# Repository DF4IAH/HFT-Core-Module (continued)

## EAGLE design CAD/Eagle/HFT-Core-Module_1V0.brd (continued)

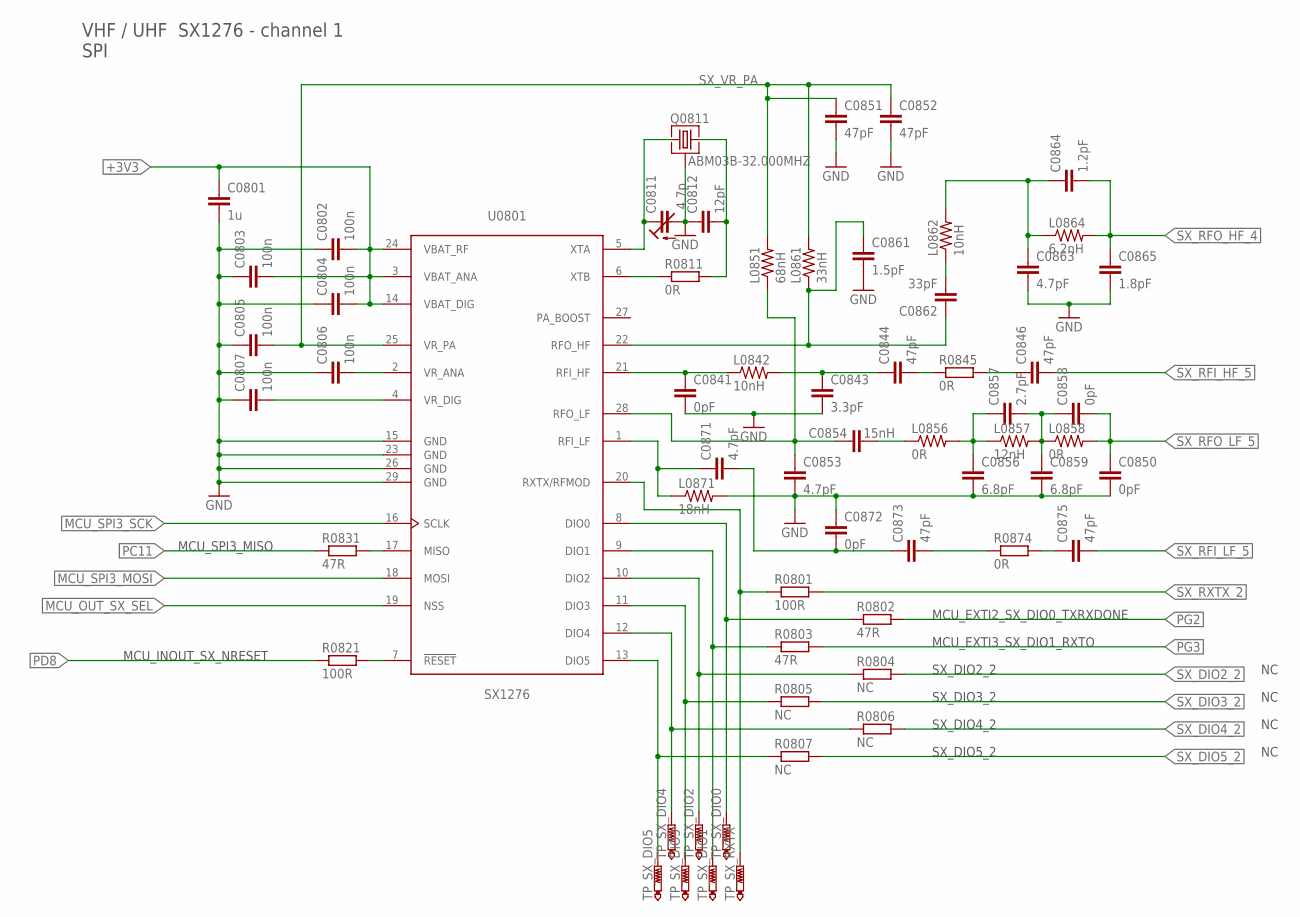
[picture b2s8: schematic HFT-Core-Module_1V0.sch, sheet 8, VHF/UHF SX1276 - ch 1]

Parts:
C0801: 1u; C0603
C0802, C0803, C0804, C0805, C0806, C0807: 100n; C0603
C0811: 4.7p; 3MM2_X_2MM5
C0812: 12pF; C0603
C0841, C0850, C0858, C0872: 0pF; C0603
C0843: 3.3pF; C0603
C0844, C0846, C0851, C0852, C0873, C0875: 47pF; C0603
C0853, C0863, C0871: 4.7pF; C0603
C0854: 15nH; C0603
C0856, C0859: 6.8pF; C0603
C0857: 2.7pF; C0603
C0861: 1.5pF; C0603
C0862: 33pF; C0603
C0864: 1.2pF; C0603
C0865: 1.8pF; C0603
L0842, L0862: 10nH; R0603
L0851: 68nH; R0603
L0856, L0858: 0R; R0603
L0857: 12nH; R0603
L0861: 33nH; R0603
L0864: 6.2nH; R0603
L0871: 18nH; R0603
Q0811: ABM03B-32.000MHZ; ABM03B
R0801, R0821: 100R; R0603
R0802, R0803, R0831: 47R; R0603
R0804, R0805, R0806, R0807: NC; R0603
R0811, R0845, R0874: 0R; R0603
TP_SX_DIO0, TP_SX_DIO1, TP_SX_DIO2, TP_SX_DIO3, TP_SX_DIO4, TP_SX_DIO5: PTR1TP06R; TP06R
TP_SX_RXTX: PTR1TP06R; TP06R
U0801: SX1276; QFN28-6X6-0P65-PAD

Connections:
+3V3: C0801.1, C0802.2, C0803.2, C0804.2, U0801.3 (VBAT_ANA), U0801.14 (VBAT_DIG), U0801.24 (VBAT_RF); also elsewhere on the board
GND: C0801.2, C0802.1, C0803.1, C0804.1, C0805.1, C0806.1, C0807.1, C0811.+ (A), C0812.1, C0841.2, C0843.2, C0850.2, C0851.2, C0852.2, C0853.2, C0856.2, C0859.2, C0861.2, C0863.2, C0865.2, C0872.1, L0871.2, Q0811.2 (3), Q0811.4 (3), U0801.15 (GND), U0801.23 (GND), U0801.26 (GND), U0801.29 (GND); also elsewhere on the board
MCU_OUT_SX_SEL: U0801.19 (NSS); also elsewhere on the board
MCU_SPI3_MOSI: U0801.18 (MOSI); also elsewhere on the board
MCU_SPI3_SCK: U0801.16 (SCLK); also elsewhere on the board
PC11: R0831.1; also elsewhere on the board
PD8: R0821.1; also elsewhere on the board
PG2: R0802.2; also elsewhere on the board
PG3: R0803.2; also elsewhere on the board
SX_DIO0: R0802.1, TP_SX_DIO0.TP, U0801.8 (DIO0)
SX_DIO1: R0803.1, TP_SX_DIO1.TP, U0801.9 (DIO1)
SX_DIO2: R0804.1, TP_SX_DIO2.TP, U0801.10 (DIO2)
SX_DIO2_2: R0804.2
SX_DIO3: R0805.1, TP_SX_DIO3.TP, U0801.11 (DIO3)
SX_DIO3_2: R0805.2
SX_DIO4: R0806.1, TP_SX_DIO4.TP, U0801.12 (DIO4)
SX_DIO4_2: R0806.2
SX_DIO5: R0807.1, TP_SX_DIO5.TP, U0801.13 (DIO5)
SX_DIO5_2: R0807.2
SX_MISO: R0831.2, U0801.17 (MISO)
SX_NRESET: R0821.2, U0801.7 (!RESET)
SX_RFI_HF: C0841.1, L0842.1, U0801.21 (RFI_HF)
SX_RFI_HF_2: C0843.1, C0844.1, L0842.2
SX_RFI_HF_3: C0844.2, R0845.1
SX_RFI_HF_4: C0846.1, R0845.2
SX_RFI_HF_5: C0846.2; also elsewhere on the board
SX_RFI_LF: C0871.1, L0871.1, U0801.1 (RFI_LF)
SX_RFI_LF_2: C0871.2, C0872.2, C0873.1
SX_RFI_LF_3: C0873.2, R0874.1
SX_RFI_LF_4: C0875.1, R0874.2
SX_RFI_LF_5: C0875.2; also elsewhere on the board
SX_RFO_HF: C0861.1, C0862.1, L0861.1, U0801.22 (RFO_HF)
SX_RFO_HF_2: C0862.2, L0862.1
SX_RFO_HF_3: C0863.1, C0864.1, L0862.2, L0864.1
SX_RFO_HF_4: C0864.2, C0865.1, L0864.2; also elsewhere on the board
SX_RFO_LF: C0853.1, C0854.1, L0851.1, U0801.28 (RFO_LF)
SX_RFO_LF_2: C0854.2, L0856.1
SX_RFO_LF_3: C0856.1, C0857.1, L0856.2, L0857.1
SX_RFO_LF_4: C0857.2, C0858.1, C0859.1, L0857.2, L0858.1
SX_RFO_LF_5: C0850.1, C0858.2, L0858.2; also elsewhere on the board
SX_RXTX: R0801.1, TP_SX_RXTX.TP, U0801.20 (RXTX/RFMOD)
SX_RXTX_2: R0801.2; also elsewhere on the board
SX_VR_ANA: C0806.2, U0801.2 (VR_ANA)
SX_VR_DIG: C0807.2, U0801.4 (VR_DIG)
SX_VR_PA: C0805.2, C0851.1, C0852.1, L0851.2, L0861.2, U0801.25 (VR_PA)
SX_XTA: C0811.- (E), Q0811.1, U0801.5 (XTA)
SX_XTB: R0811.1, U0801.6 (XTB)
SX_XTB_R: C0812.2, Q0811.3 (2), R0811.2

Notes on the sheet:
VHF / UHF SX1276 - channel 1 SPI
MCU_SPI3_MISO
MCU_INOUT_SX_NRESET
MCU_EXTI2_SX_DIO0_TXRXDONE
MCU_EXTI3_SX_DIO1_RXTO
SX_DIO2_2
SX_DIO3_2
SX_DIO4_2
SX_DIO5_2

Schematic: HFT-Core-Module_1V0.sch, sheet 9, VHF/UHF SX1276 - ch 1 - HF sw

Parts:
C0911, C0921, C0999: 1nF; C0603
C0991: 100pF HiQ; C0603
C0992, C0993: 330pF HiQ; C0603
C0994, C0996: 0nF HiQ; C0603
L0995: 0R; R0603
U0911, U0921, U0991: PE4259; SC-70_6-LEAD_2X1MM25_0P65

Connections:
+3V3: C0911.1, C0921.1, C0999.1, U0911.6 (VDD_!CTRL), U0921.6 (VDD_!CTRL), U0991.6 (VDD_!CTRL); also elsewhere on the board
CH1_ANT: C0996.1, L0995.2; also elsewhere on the board
GND: C0911.2, C0921.2, C0994.2, C0996.2, C0999.2, U0911.2 (GND), U0921.2 (GND), U0991.2 (GND); also elsewhere on the board
MCU_SX_TX_RX_CTRL: U0991.4 (CTRL); also elsewhere on the board
SX_ANT_1: C0993.1, U0991.5 (RFC)
SX_ANT_2: C0993.2, C0994.1, L0995.1
SX_HF_1: C0991.1, U0911.5 (RFC)
SX_HF_2: C0991.2, U0991.1 (RF1)
SX_LF_1: C0992.1, U0921.5 (RFC)
SX_LF_2: C0992.2, U0991.3 (RF2)
SX_RFI_HF_5: U0911.3 (RF2); also elsewhere on the board
SX_RFI_LF_5: U0921.3 (RF2); also elsewhere on the board
SX_RFO_HF_4: U0911.1 (RF1); also elsewhere on the board
SX_RFO_LF_5: U0921.1 (RF1); also elsewhere on the board
SX_RXTX_2: U0911.4 (CTRL), U0921.4 (CTRL); also elsewhere on the board

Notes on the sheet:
HF: high / LF: low

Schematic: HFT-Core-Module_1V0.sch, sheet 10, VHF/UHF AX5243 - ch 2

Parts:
C1001, C1002, C1003: 100nF; C0603
C_AX_A2, C_AX_A3: 4.7pF; C0603
C_AX_B2: 4.7pF; C0603
C_AX_C1, C_AX_C2: 0pF; C0603
C_AX_F2: 4.7pF; C0603
C_AX_M1: 4.7pF; C0603
C_AX_M2: 0pF; C0603
C_AX_T1, C_AX_T2: 4.3pF; C0603
L_AX_1: 22nH; R0603
L_AX_B1, L_AX_B2: 22nH; R0603
L_AX_C1, L_AX_C2: 100nH; R0603
L_AX_F1: 22nH; R0603
L_AX_T1, L_AX_T2: 43nH; R0603
Q0911: ABM3B-16MHZ-10-R50-1-U; ABM03B
R1021, R1041, R1051, R1061: 47R; R0603
R1031, R1032: 100kR; R0603
TP_AX_ADC1, TP_AX_ADC2: PTR1TP06R; TP06R
TP_AX_IRQ: PTR1TP06R; TP06R
TP_AX_TCXO_EN: PTR1TP06R; TP06R
U0901: AX5243; QFN20-4X4-0P5-PAD

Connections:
+3V3: C1001.1, U0901.16 (VDD_IO); also elsewhere on the board
AX_8MHZ: R1021.2; also elsewhere on the board
AX_ADC1: R1031.1, TP_AX_ADC1.TP, U0901.17 (GPADC1)
AX_ADC2: R1032.1, TP_AX_ADC2.TP, U0901.18 (GPADC2)
AX_ANTN: C_AX_C2.1, C_AX_T2.1, L_AX_C2.1, U0901.4 (ANTN)
AX_ANTP: C_AX_C1.1, C_AX_T1.1, L_AX_C1.1, U0901.3 (ANTP)
AX_B1: C_AX_M1.1, L_AX_B1.1, L_AX_T1.2
AX_B2: C_AX_B2.1, C_AX_M2.1, L_AX_B2.2, L_AX_T2.2
AX_CLK16N: Q0911.1, U0901.19 (CLK16N)
AX_CLK16P: Q0911.3 (2), U0901.20 (CLK16P)
AX_COMB: C_AX_A2.1, C_AX_B2.2, C_AX_F2.1, L_AX_B1.2, L_AX_F1.1
AX_GPIO1: R1061.2, TP_AX_TCXO_EN.TP, U0901.15 (TCXO_EN)
AX_IRQ: R1051.2, TP_AX_IRQ.TP, U0901.14 (IRQ)
AX_L1: L_AX_1.1, U0901.8 (L1)
AX_L2: L_AX_1.2, U0901.7 (L2)
AX_SYSCLK: R1021.1, U0901.9 (SYSCLK)
AX_T1: C_AX_T1.2, L_AX_T1.1
AX_T2: C_AX_T2.2, L_AX_T2.1
AX_VDD1: C1002.2, U0901.1 (VDD_ANA)
AX_VDD5: C1003.2, U0901.5 (VDD_ANA)
CH2_ANT: C_AX_A3.1, C_AX_F2.2, L_AX_F1.2; also elsewhere on the board
GND: C1001.2, C1002.1, C1003.1, C_AX_A2.2, C_AX_A3.2, C_AX_C1.2, C_AX_C2.2, C_AX_M1.2, C_AX_M2.2, L_AX_B2.1, L_AX_C1.2, L_AX_C2.2, Q0911.2 (3), Q0911.4 (3), R1031.2, R1032.2, U0901.2 (GND), U0901.21 (GND); also elsewhere on the board
MCU_AX_MISO: R1041.2, U0901.12 (MISO)
MCU_OUT_AX_SEL: U0901.10 (SEL); also elsewhere on the board
MCU_SPI3_MOSI: U0901.13 (MOSI); also elsewhere on the board
MCU_SPI3_SCK: U0901.11 (CLK); also elsewhere on the board
PC11: R1041.1; also elsewhere on the board
PE7: R1051.1; also elsewhere on the board
PG1: R1061.1; also elsewhere on the board

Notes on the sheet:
VHF / UHF AX5243 - channel 2 SPI

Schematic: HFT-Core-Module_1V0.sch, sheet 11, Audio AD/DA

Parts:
C1101, C1102, C1103, C1111, C1112, C1128, C1129: 100nF; C0603
C1104, C1105, C1131, C1141: 220nF; C0603
C1113: 47pF; C0603
C1132, C1142: 100uF; C0805
L1102, L1112: 10uH; L2012C
R1104, R1105: 22kR; R0603
R1106, R1107, R1108, R1109, R1114: 47R; R0603
R1110: 33kR; R0603
R1131, R1141: 10kR; R0603
R1132, R1135, R1142, R1145: 10MR; R0603
U1101: MCP3911A0-E-SS; QFN20_P0MM5_CTRPAD
U1111: MAX5136AGTG+; QFN24_P0MM5_CTRPAD
U1121, U1131, U1141: OPA354; SOT-23-5

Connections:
+3V3_HICUR: C1101.1, C1111.1, C1128.1, C1129.1, L1102.2, L1112.2, U1101.19 (DVDD), U1111.3 (DVDD), U1111.15 (!LDAC), U1121.5 (V+), U1131.5 (V+), U1141.5 (V+); also elsewhere on the board
AUDIO_IN_L: C1104.1; also elsewhere on the board
AUDIO_IN_R: C1105.1; also elsewhere on the board
AUDIO_OUT_L: C1132.2; also elsewhere on the board
AUDIO_OUT_L_OP: C1132.1, U1131.1 (OUT), U1131.4 (-IN)
AUDIO_OUT_R: C1142.2; also elsewhere on the board
AUDIO_OUT_R_OP: C1142.1, U1141.1 (OUT), U1141.4 (-IN)
GND: C1101.2, C1102.1, C1103.1, C1111.2, C1112.1, C1113.2, C1128.2, C1129.2, R1104.1, R1105.1, R1110.1, R1135.1, R1145.1, U1101.2 (CH0-), U1101.4 (CH1-), U1101.5 (AGND), U1101.7 (REFIN-), U1101.8 (DGND), U1101.21 (DGND), U1111.7 (GND), U1111.19 (GND), U1111.25 (GND), U1121.2 (V-), U1131.2 (V-), U1141.2 (V-); also elsewhere on the board
MAX5136_!READY: R1114.2, U1111.4 (!READY)
MAX5136_AVDD: C1112.2, L1112.1, U1111.16 (M/!Z), U1111.24 (AVDD)
MAX5136_OUT0: R1131.1, U1111.1 (OUT0)
MAX5136_OUT0_R: C1131.1, R1131.2
MAX5136_OUT0_SUM: C1131.2, R1132.2, R1135.2, U1131.3 (+IN)
MAX5136_OUT1: R1141.1, U1111.18 (OUT1)
MAX5136_OUT1_R: C1141.1, R1141.2
MAX5136_OUT1_SUM: C1141.2, R1142.2, R1145.2, U1141.3 (+IN)
MAX5136_REF: C1113.1, U1111.21 (REFO), U1111.22 (REFI), U1121.3 (+IN)
MAX5136_REF_OP: R1132.1, R1142.1, U1121.1 (OUT), U1121.4 (-IN)
MCP3911_!DR: R1106.1, U1101.11 (!DR)
MCP3911_CH0+: C1104.2, R1104.2, U1101.1 (CH0+)
MCP3911_CH1+: C1105.2, R1105.2, U1101.3 (CH1+)
MCP3911_MDAT0: R1108.1, U1101.10 (MDAT0)
MCP3911_MDAT1: R1109.1, U1101.9 (MDAT1)
MCP3911_REFINOUT: C1103.2, U1101.6 (REFINOUT)
MCP3911_SDO: R1107.1, U1101.16 (SDO)
MCU_OUT_AUDIO_ADC_NRESET: R1110.2, U1101.18 (!RESET); also elsewhere on the board
MCU_OUT_AUDIO_ADC_SEL: U1101.14 (!CS); also elsewhere on the board
MCU_OUT_AUDIO_DAC_SEL: U1111.10 (!CS); also elsewhere on the board
MCU_SPI3_MOSI: U1101.17 (SDI), U1111.9 (DIN); also elsewhere on the board
MCU_SPI3_SCK: U1101.15 (SCK), U1111.12 (SCLK); also elsewhere on the board
MVP3911_AVDD: C1102.2, L1102.1, U1101.20 (AVDD)
PC8: R1114.1; also elsewhere on the board
PC11: R1107.2; also elsewhere on the board
PD0: R1109.2; also elsewhere on the board
PD1: R1108.2; also elsewhere on the board
PD2: R1106.2; also elsewhere on the board
SI5338_CLK3B_2: U1101.12 (OSC1); also elsewhere on the board

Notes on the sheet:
Audio stereo A/D-Converter SPI
N.C. (should be connected to GND)
10MHz
Audio stereo D/A-Converter SPI
MCU_IN_AUDIO_DAC_NRDY
MCU_IN_AUDIO_ADC_MDAT0
MCU_IN_AUDIO_ADC_MDAT1
MCU_IN_AUDIO_ADC_NDR
MCU_SPI3_MISO

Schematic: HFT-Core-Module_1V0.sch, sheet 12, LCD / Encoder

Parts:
C1211, C1221: 1uF; C0805
C1231: 100nF; C0603
C1261, C1262, C1271: 1nF; C0603
R1201, R1204, R1207: 2.0kR; R0603
R1202, R1205, R1208: 1.5kR; R0603
R1203, R1206, R1209: 27R; R0805
R1241: 33kR; R0603
R1261, R1262, R1271: 10kR; R0603
T1201, T1202, T1203: MMBT2222; SOT23
U1201: NHD-C0220BIZ_2X20CHARS
X1261: TTE_EN11-HSM

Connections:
+3V3: C1231.1, U1201.5 (VDD), U1201.12 (A); also elsewhere on the board
GND: C1221.2, C1231.2, C1261.2, C1262.2, C1271.2, R1202.1, R1203.1, R1205.1, R1206.1, R1208.1, R1209.1, R1241.1, U1201.4 (VSS), X1261.C, X1261.D; also elsewhere on the board
LCD_C1+: C1211.2, U1201.7 (C1+)
LCD_C1-: C1211.1, U1201.8 (C1-)
LCD_VOUT: C1221.1, U1201.6 (VOUT)
LED_B_B: R1207.1, R1208.2, T1203.1 (B)
LED_B_E: R1209.2, T1203.2 (E)
LED_B_K: T1203.3 (C), U1201.11 (KB)
LED_G_B: R1204.1, R1205.2, T1202.1 (B)
LED_G_E: R1206.2, T1202.2 (E)
LED_G_K: T1202.3 (C), U1201.10 (KG)
LED_R_B: R1201.1, R1202.2, T1201.1 (B)
LED_R_E: R1203.2, T1201.2 (E)
LED_R_K: T1201.3 (C), U1201.9 (KR)
MCU_I2C4_SCL: U1201.2 (SCL); also elsewhere on the board
MCU_I2C4_SDA: U1201.3 (SDA); also elsewhere on the board
MCU_OUT_LCD_NRST: R1241.2, U1201.1 (RST); also elsewhere on the board
PA7: R1204.2; also elsewhere on the board
PB0: R1207.2; also elsewhere on the board
PB10: R1261.2; also elsewhere on the board
PB12: R1262.2; also elsewhere on the board
PB14: R1271.2; also elsewhere on the board
PC6: R1201.2; also elsewhere on the board
ROTENC_A: C1261.1, R1261.1, X1261.A
ROTENC_B: C1262.1, R1262.1, X1261.B
ROTENC_E: C1271.1, R1271.1, X1261.E

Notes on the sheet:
LCD: 2x20 chars NHD-C0220BIZ-FS(RGB)-FBW-3VM-ND
LC-Display I2C addr: 0x3E
Rotary Encoder with Pushbutton
MCU_PWM_LED_R
MCU_PWM_LED_G
MCU_PWM_LED_B
MCU_IN_RE_I
MCU_IN_RE_Q
MCU_IN_RE_PB

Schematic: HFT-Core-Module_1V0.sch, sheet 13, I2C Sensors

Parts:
C1301, C1303, C1311, C1321: 100nF; C0603
C1302: 10nF; C0603
R1301: 68R; R0603
R1331, R1332: 1.0kR; R0603
U1301: MPU-9250; QFN24-3X3
U1311: MS5607-02BA03; MS5607-02BA
U1321: SHT31-DIS; DFN8/SHT

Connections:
+3V3: C1301.1, C1302.1, C1311.1, C1321.1, R1331.2, R1332.2, U1301.1 (VDDIO), U1301.8 (VDDIO), U1301.13 (VDD), U1301.22 (!CS), U1311.1 (VDD), U1311.2 (PS), U1311.4 (CSB_!ADDR), U1321.5 (VDD), U1321.6 (!RESET); also elsewhere on the board
GND: C1301.2, C1302.2, C1303.2, C1311.2, C1321.2, U1301.9 (AD0/SDO), U1301.11 (FSYNC), U1301.18 (GND), U1301.20 (GND), U1311.3 (GND), U1321.2 (ADDR), U1321.7 (R), U1321.8 (VSS), U1321.9 (PAD); also elsewhere on the board
MCU_I2C4_SCL: R1332.1, U1301.23 (SCL/SCLK), U1311.8 (SCL_SCLK), U1321.4 (SCL); also elsewhere on the board
MCU_I2C4_SDA: R1331.1, U1301.24 (SDA/SDI), U1311.7 (SDI_SDA), U1321.1 (SDA); also elsewhere on the board
MPU_INT: R1301.1, U1301.12 (INT)
MPU_REGOUT: C1303.1, U1301.10 (REGOUT)
PF13: R1301.2; also elsewhere on the board

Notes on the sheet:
Baro sensor: MS5607-02BA03 I2C addr: 0x76
9-axis sensor: MPU-9250 I2C addr: 0x68, 0x0C
RH sensor: Sensirion SHT3x I2C addr: 0x44
I2C4 Termination
I2C2_INT

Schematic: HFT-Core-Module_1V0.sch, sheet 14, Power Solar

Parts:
C1401: 100uF; C0805
C1402, C1403: 100nF; C0603
C1404: 10uF; C0805
C1405: 0nF; C0603
C1406: 47uF; C0805
D1403: CRS08; SOD80C
L1403: 33uH; L_13.5X12.5MM
R1404, R1405, R1406, R1409: 0R; R0603
R1407, R1412: 100kR; R0603
R1408: 310kR; R0603
R1411: 1kR; R0603
TP_+5V0_SOL: PTR1B1,27; B1,27
TP_VSOL: PTR1B1,27; B1,27
U1401: SOLARPANEL_3V3_5MA1_25MM_X_20MM
U1402: SPV1040T; TSSOP8

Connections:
+5V0: R1409.2; also elsewhere on the board
+5V1_SOL: C1406.1, R1405.2, R1406.2, R1408.2, R1409.1, TP_+5V0_SOL.TP
GND: C1401.2, C1402.2, C1403.2, C1404.2, C1406.2, R1407.1, U1401.-VSOL, U1402.2 (GND); also elsewhere on the board
PA3: R1411.2; also elsewhere on the board
PF9: R1412.1; also elsewhere on the board
SPV_ICTRL_M: C1405.2, R1405.1, U1402.6 (ICTRL_M)
SPV_ICTRL_P: C1405.1, R1404.1, U1402.7 (ICTRL_P)
SPV_LX: D1403.A, L1403.1, R1412.2, U1402.3 (LX)
SPV_VCTRL: R1407.2, R1408.1, U1402.5 (VCTRL)
SPV_VOUT: C1403.1, C1404.1, D1403.C, R1404.2, R1406.1, U1402.4 (VOUT)
VSOL: C1401.1, C1402.1, L1403.2, R1411.1, TP_VSOL.TP, U1401.+VSOL, U1402.1 (MPP_SET), U1402.8 (XSHUT)

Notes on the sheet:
1V25
Imax:50mV
13.5mm x 12.5mm
DC/DC boost converter
Imax disabled
Solar power converter
MCU_VSOL_ADC1
MCU_VSOL_TIMCAP

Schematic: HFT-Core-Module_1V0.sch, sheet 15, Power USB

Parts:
C1501: 100nF; C0603
D1501: CRS08; SOD80C
R1502: 33kR; R0603
TP_+5V0_USB_SW: PTR1B1,27; B1,27
U1501: TS5A23166; R-PDSO-G8

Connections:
+5V0: D1501.C; also elsewhere on the board
GND: C1501.2, R1502.1, U1501.4; also elsewhere on the board
MCU_OUT_VUSB_EN: R1502.2, U1501.3, U1501.7; also elsewhere on the board
VDDUSB: C1501.1, U1501.1, U1501.5, U1501.8; also elsewhere on the board
VUSB_SW: D1501.A, TP_+5V0_USB_SW.TP, U1501.2, U1501.6

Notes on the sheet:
Electronic switch for USB <--> 5V

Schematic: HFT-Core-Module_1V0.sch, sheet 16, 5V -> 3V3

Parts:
C1601, C1607: 1F_EEC-S5R5H105N; W14MM_D8MM_P13MM5
C1602, C1606: 47uF; C0805
C1605: 100nF; C0603
L1604: 1.0uH 33mR; L5650M
TP_+3V3, TP_+5V0: PTR1B1,27; B1,27
U1601: SC189ZSKTRT; SOT95P280X145-5N

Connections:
+3V3: C1605.1, C1606.1, C1607.+, L1604.1, TP_+3V3.TP, U1601.4 (VOUT_FB); also elsewhere on the board
+5V0: C1601.+, C1602.1, TP_+5V0.TP, U1601.1 (VIN), U1601.3 (EN); also elsewhere on the board
GND: C1601.-, C1602.2, C1605.2, C1606.2, C1607.-, U1601.2 (GND); also elsewhere on the board
SW: L1604.2, U1601.5 (SW)

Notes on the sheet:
5mm x 5mm
DC/DC buck converter
Power converter 5V --> 3.3V
(1.5A out, 1.5MHz fixed)
(replaces PAM2305)

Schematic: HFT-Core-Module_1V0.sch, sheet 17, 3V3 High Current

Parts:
C1701, C1703: 100nF; C0603
R1702: 33kR; R0603
TP_+3V3_HICUR: PTR1B1,27; B1,27
U1701: TS5A23166; R-PDSO-G8

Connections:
+3V3: C1701.1, U1701.1, U1701.5, U1701.8; also elsewhere on the board
+3V3_HICUR: C1703.1, TP_+3V3_HICUR.TP, U1701.2, U1701.6; also elsewhere on the board
GND: C1701.2, C1703.2, R1702.1, U1701.4; also elsewhere on the board
MCU_OUT_HICUR_EN: R1702.2, U1701.3, U1701.7; also elsewhere on the board

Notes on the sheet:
Electronic switch for clock distribution unit

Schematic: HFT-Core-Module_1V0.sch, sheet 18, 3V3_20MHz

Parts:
C1801, C1803: 100nF; C0603
R1802: 33kR; R0603
TP_+3V3_20MHZ: PTR1B1,27; B1,27
U1801: TS5A23166; R-PDSO-G8

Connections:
+3V3: C1801.1, U1801.1, U1801.5, U1801.8; also elsewhere on the board
+3V3_20MHZ: C1803.1, TP_+3V3_20MHZ.TP, U1801.2, U1801.6; also elsewhere on the board
GND: C1801.2, C1803.2, R1802.1, U1801.4; also elsewhere on the board
MCU_OUT_20MHZ_EN: R1802.2, U1801.3, U1801.7; also elsewhere on the board

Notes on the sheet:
Electronic switch for TCXO unit

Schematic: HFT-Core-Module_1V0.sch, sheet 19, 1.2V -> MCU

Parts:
C1901, C1902, C1903, C1908, C1909: 100nF; C0603
R1902: 33kR; R0603
TP_+1V2_MCU: PTR1B1,27; B1,27
U1901: TS5A23166; R-PDSO-G8

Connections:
+1V2: C1901.1, U1901.1, U1901.5; also elsewhere on the board
+3V3: C1902.1, U1901.8; also elsewhere on the board
GND: C1901.2, C1902.2, C1903.2, C1908.1, C1909.2, R1902.1, U1901.4; also elsewhere on the board
MCU_OUT_VDD12_EN: R1902.2, U1901.3, U1901.7; also elsewhere on the board
MCU_VDD12: C1903.1, C1908.2, C1909.1, TP_+1V2_MCU.TP, U1901.2, U1901.6; also elsewhere on the board

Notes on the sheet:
Electronic switch for MCU SMTP ext. 1.2V

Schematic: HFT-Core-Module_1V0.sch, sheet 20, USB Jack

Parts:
C2003: 1nF; C0603
PF2011: 1.1A/2.2A; M1206
R2002: 330kR; R0603
X2001: MOLEX 105017-0001; USB-B-MICRO-SMD_MOLEX-105017-0001

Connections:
GND: C2003.1, R2002.1, X2001.GND; also elsewhere on the board
PA9: PF2011.1, X2001.VBUS (J_VUSB); also elsewhere on the board
PA10: X2001.ID (J_ID); also elsewhere on the board
PA_USB_N: X2001.D- (J_D-); also elsewhere on the board
PA_USB_P: X2001.D+ (J_D+); also elsewhere on the board
USB_SHIELD: C2003.2, R2002.2, X2001.JSHIELD (SHIELD), X2001.JSHIELD@2 (SHIELD), X2001.JSHIELD@3 (SHIELD), X2001.JSHIELD@4 (SHIELD), X2001.JSHIELD@5 (SHIELD), X2001.JSHIELD@6 (SHIELD)
VDDUSB: PF2011.2; also elsewhere on the board

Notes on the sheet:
Impedance 90 Ohms
USB device and USB host (OTG) interface
MCU_USB_DM
MCU_USB_DP
MCU_USB_ID
MCU_USB_OTG_FS_VBUS
LITTLEFUSE 1206L050YR

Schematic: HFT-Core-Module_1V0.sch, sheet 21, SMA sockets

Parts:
X2101, X2111: SMA_SMT_AMPHENOL-901-143, SAMTEC SMA-J-P-H-RA-TH1; SMA_SMT_AMPHENOL_901-143

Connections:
CH1_ANT: X2101.1; also elsewhere on the board
CH2_ANT: X2111.1; also elsewhere on the board
GND: X2101.2, X2101.3 (2), X2101.4 (2), X2101.5 (2), X2111.2, X2111.3 (2), X2111.4 (2), X2111.5 (2); also elsewhere on the board

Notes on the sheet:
SMA channel 1
SMA channel 2

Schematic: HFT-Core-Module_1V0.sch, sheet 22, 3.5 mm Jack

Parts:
X2201, X2211: CUI SJ1-3535NS; SJ1-353XNS_3MM5-STEREO-AUDIO-JACKS

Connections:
AUDIO_IN_L: X2201.2 (TIP); also elsewhere on the board
AUDIO_IN_R: X2201.3 (RING); also elsewhere on the board
AUDIO_OUT_L: X2211.2 (TIP); also elsewhere on the board
AUDIO_OUT_R: X2211.3 (RING); also elsewhere on the board
GND: X2201.1 (SLEEVE), X2201.6 (GND), X2201.7 (GND), X2201.8 (GND), X2211.1 (SLEEVE), X2211.6 (GND), X2211.7 (GND), X2211.8 (GND); also elsewhere on the board

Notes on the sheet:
Audio connectors
AUDIO IN
AUDIO OUT

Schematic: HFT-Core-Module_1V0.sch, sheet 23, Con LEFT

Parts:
R2310, R2311, R2312, R2313, R2314, R2315, R2316, R2317, R2318, R2320, R2321, R2322, R2323, R2324, R2325, R2326, R2327, R2328, R2330, R2331, R2332, R2333, R2334, R2335, R2336, R2337, R2338: 47R; R0603
X2311, X2312, X2321, X2322, X2331, X2332: 2X20/90_1MM27_HARWIN_M50-3202045

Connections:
+3V3: X2311.3, X2311.4, X2312.37, X2312.38, X2321.3, X2321.4, X2322.37, X2322.38, X2331.3, X2331.4, X2332.37, X2332.38; also elsewhere on the board
+5V0: X2311.37, X2311.38, X2321.37, X2321.38, X2331.37, X2331.38; also elsewhere on the board
CLK0_N: X2332.4; also elsewhere on the board
CLK0_P: X2332.3; also elsewhere on the board
CLK1_N: X2322.4; also elsewhere on the board
CLK1_P: X2322.3; also elsewhere on the board
CLK2_N: X2312.4; also elsewhere on the board
CLK2_P: X2312.3; also elsewhere on the board
EVT_N: R2314.2, X2311.29
EVT_S: R2334.2, X2331.29
EVT_W: R2324.2, X2321.29
GND: X2311.1, X2311.2, X2311.5, X2311.6, X2311.8, X2311.10, X2311.12, X2311.14, X2311.21, X2311.22, X2311.27, X2311.28, X2311.30, X2311.32, X2311.34, X2311.35, X2311.36, X2311.39, X2311.40, X2312.1, X2312.2, X2312.5, X2312.6, X2312.9, X2312.10, X2312.14, X2312.15, X2312.16, X2312.21, X2312.22, X2312.25, X2312.27, X2312.28, X2312.39, X2312.40, X2321.1, X2321.2, X2321.5, X2321.6, X2321.8, X2321.10, X2321.12, X2321.14, X2321.21, X2321.22, X2321.27, X2321.28, X2321.30, X2321.32, X2321.34, X2321.35, X2321.36, X2321.39, X2321.40, X2322.1, X2322.2, X2322.5, X2322.6, X2322.9, X2322.10, X2322.14, X2322.15, X2322.16, X2322.21, X2322.22, X2322.25, X2322.27, X2322.28, X2322.39, X2322.40, X2331.1, X2331.2, X2331.5, X2331.6, X2331.8, X2331.10, X2331.12, X2331.14, X2331.21, X2331.22, X2331.27, X2331.28, X2331.30, X2331.32, X2331.34, X2331.35, X2331.36, X2331.39, X2331.40, X2332.1, X2332.2, X2332.5, X2332.6, X2332.9, X2332.10, X2332.14, X2332.15, X2332.16, X2332.21, X2332.22, X2332.25, X2332.27, X2332.28, X2332.39, X2332.40; also elsewhere on the board
I2S_FS_IN_N: R2317.2, X2312.26
I2S_FS_IN_S: R2337.2, X2332.26
I2S_FS_IN_W: R2327.2, X2322.26
I2S_FS_OUT: X2312.20, X2322.20, X2332.20; also elsewhere on the board
I2S_MCLK_OUT: X2312.19, X2322.19, X2332.19; also elsewhere on the board
I2S_SCK_IN_N: R2315.2, X2312.23
I2S_SCK_IN_S: R2335.2, X2332.23
I2S_SCK_IN_W: R2325.2, X2322.23
I2S_SCK_OUT: X2312.17, X2322.17, X2332.17; also elsewhere on the board
I2S_SD_IN_N: R2316.2, X2312.24
I2S_SD_IN_S: R2336.2, X2332.24
I2S_SD_IN_W: R2326.2, X2322.24
I2S_SD_OUT: X2312.18, X2322.18, X2332.18; also elsewhere on the board
MCU_I2C1_SCL: X2312.7; also elsewhere on the board
MCU_I2C1_SDA: X2312.8; also elsewhere on the board
MCU_I2C2_SCL: X2322.7; also elsewhere on the board
MCU_I2C2_SDA: X2322.8; also elsewhere on the board
MCU_I2C3_SCL: X2332.7; also elsewhere on the board
MCU_I2C3_SDA: X2332.8; also elsewhere on the board
MCU_SPI1_MISO: X2312.12, X2322.12, X2332.12; also elsewhere on the board
MCU_SPI1_MOSI: X2312.11, X2322.11, X2332.11; also elsewhere on the board
MCU_SPI1_SCK: X2312.13, X2322.13, X2332.13; also elsewhere on the board
MCU_WAKEUP: X2311.33, X2321.33, X2331.33; also elsewhere on the board
PB3: R2310.1; also elsewhere on the board
PB5: R2311.1; also elsewhere on the board
PB6: R2312.1; also elsewhere on the board
PB7: R2313.1; also elsewhere on the board
PB13: R2315.1, R2325.1, R2335.1; also elsewhere on the board
PD9: R2330.1; also elsewhere on the board
PD10: R2331.1; also elsewhere on the board
PD11: R2316.1, R2326.1, R2336.1; also elsewhere on the board
PD12: R2317.1, R2327.1, R2337.1; also elsewhere on the board
PD14: R2332.1; also elsewhere on the board
PD15: R2333.1; also elsewhere on the board
PE0: R2314.1; also elsewhere on the board
PE2: R2323.1; also elsewhere on the board
PE4: R2322.1; also elsewhere on the board
PE5: R2321.1; also elsewhere on the board
PF2: R2320.1; also elsewhere on the board
PF6: R2318.1; also elsewhere on the board
PF7: R2328.1; also elsewhere on the board
PF8: R2338.1; also elsewhere on the board
PF10: R2324.1; also elsewhere on the board
PG4: R2334.1; also elsewhere on the board
PN00: R2310.2, X2311.7
PN01: R2311.2, X2311.9
PN02: R2312.2, X2311.11
PN03: R2313.2, X2311.13
PS00: R2330.2, X2331.7
PS01: R2331.2, X2331.9
PS02: R2332.2, X2331.11
PS03: R2333.2, X2331.13
PW00: R2320.2, X2321.7
PW01: R2321.2, X2321.9
PW02: R2322.2, X2321.11
PW03: R2323.2, X2321.13
TIMCAP_N: R2318.2, X2311.31
TIMCAP_S: R2338.2, X2331.31
TIMCAP_W: R2328.2, X2321.31
UART1_CTS_IN: X2311.26; also elsewhere on the board
UART1_RTS_OUT: X2311.25; also elsewhere on the board
UART1_RX_IN: X2311.24; also elsewhere on the board
UART1_TX_OUT: X2311.23; also elsewhere on the board
UART2_CTS_IN: X2321.26; also elsewhere on the board
UART2_RTS_OUT: X2321.25; also elsewhere on the board
UART2_RX_IN: X2321.24; also elsewhere on the board
UART2_TX_OUT: X2321.23; also elsewhere on the board
UART3_CTS_IN: X2331.26; also elsewhere on the board
UART3_RTS_OUT: X2331.25; also elsewhere on the board
UART3_RX_IN: X2331.24; also elsewhere on the board
UART3_TX_OUT: X2331.23; also elsewhere on the board

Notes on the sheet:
North-West
West-South
South-East
North-East
West-North
South-West
Expansion connectors

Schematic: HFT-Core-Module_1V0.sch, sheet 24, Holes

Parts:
H2401, H2402, H2403, H2404: MOUNT-PAD-ROUND2.8; 2,8-PAD

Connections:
GND: H2401.B2,8, H2402.B2,8, H2403.B2,8, H2404.B2,8; also elsewhere on the board

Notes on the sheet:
Mounting holes
